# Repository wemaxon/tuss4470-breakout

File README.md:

# tuss4470-breakout
Breakout Board for the TUSS4470 Ultrasonic Sensing IC

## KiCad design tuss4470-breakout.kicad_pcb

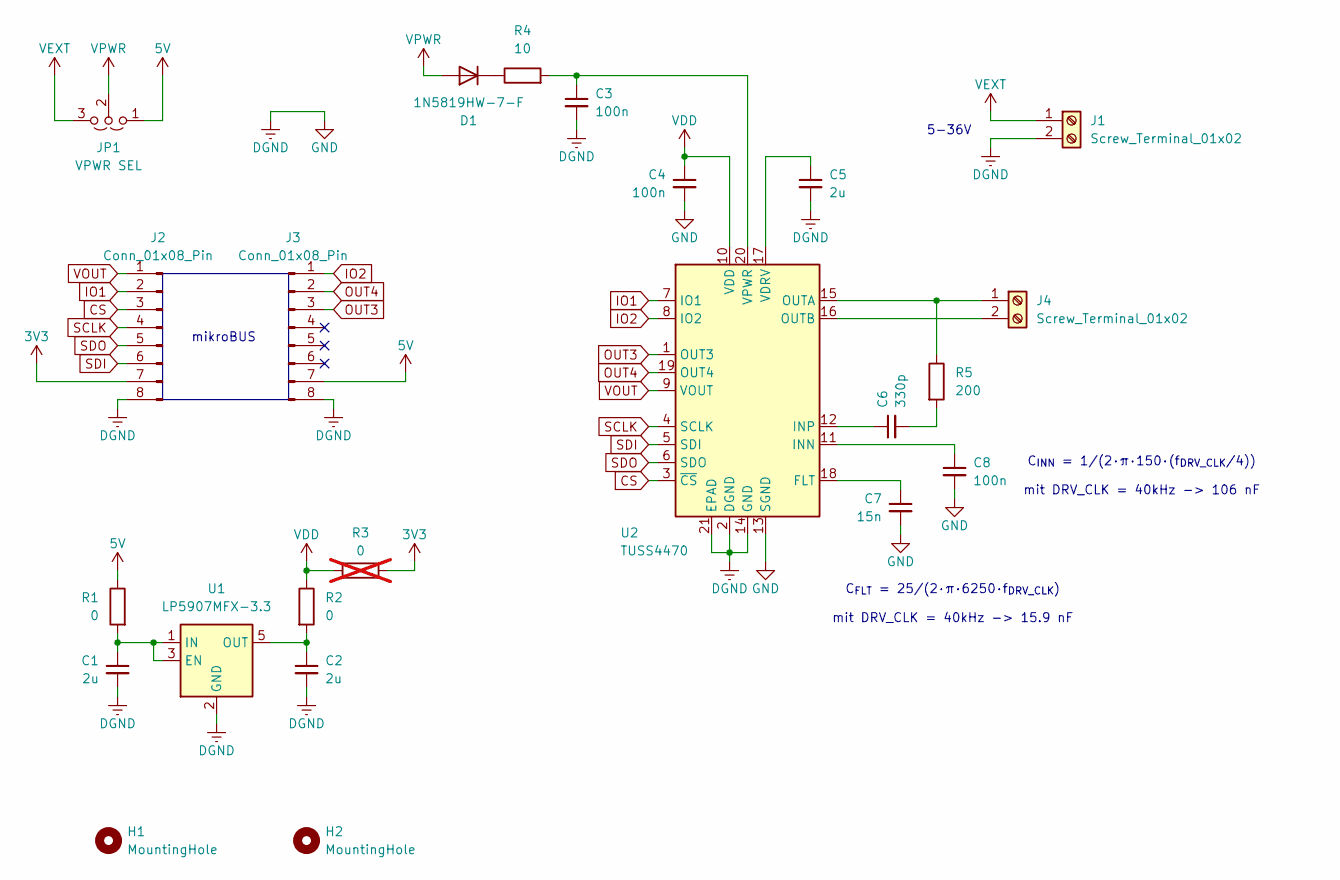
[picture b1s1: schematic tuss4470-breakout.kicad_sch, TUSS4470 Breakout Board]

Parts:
C1, C2, C5: 2u; C_0603_1608Metric; LCSC Part C913904
C3, C4, C8: 100n; C_0603_1608Metric; LCSC Part C14663
C6: 330p; C_0603_1608Metric; LCSC Part C1664
C7: 15n; C_0603_1608Metric; LCSC Part C519550
D1: 1N5819HW-7-F; D_SOD-123; LCSC Part C82544
H1, H2: MountingHole; MountingHole_3.2mm_M3
J1, J4: Screw_Terminal_01x02; TerminalBlock_Xinya_XY308-2.54-2P_1x02_P2.54mm_Horizontal; LCSC Part C557685
J2, J3: Conn_01x08_Pin; PinHeader_1x08_P2.54mm_Vertical
JP1: VPWR SEL; PinHeader_1x03_P2.54mm_Vertical
R1, R2: 0; R_0603_1608Metric; LCSC Part C95177
R3: 0; R_0603_1608Metric; LCSC Part C95177; not fitted
R4: 10; R_0805_2012Metric; LCSC Part C441940
R5: 200; R_0805_2012Metric; LCSC Part C5972814
U1: LP5907MFX-3.3; SOT-23-5; LCSC Part C80670
U2: TUSS4470; WQFN-20-1EP_4x4mm_P0.5mm_EP2.7x2.7mm_ThermalVias; LCSC Part C1855776

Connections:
3V3: J2.7, R3.1
5V: J3.7, JP1.1 (A), R1.1
CS: J2.3, U2.3 (~CS)
DGND: C1.2, C2.2, C3.2, C4.2, C5.2, C7.2, C8.2, J1.2, J2.8, J3.8, U1.2 (GND), U2.2 (DGND), U2.13 (SGND), U2.14 (GND), U2.21 (EPAD)
IO1: J2.2, U2.7 (IO1)
IO2: J3.1, U2.8 (IO2)
unnamed: C6.2, R5.2
unnamed: D1.1 (K), R4.1
unnamed: J4.1, R5.1, U2.15 (OUTA)
unnamed: J4.2, U2.16 (OUTB)
unnamed: C1.1, R1.2, U1.1 (IN), U1.3 (EN)
unnamed: C2.1, R2.2, U1.5 (OUT)
unnamed: C7.1, U2.18 (FLT)
unnamed: C8.1, U2.11 (INN)
unnamed: C6.1, U2.12 (INP)
unnamed: C5.1, U2.17 (VDRV)
unnamed: C3.1, R4.2, U2.20 (VPWR)
OUT3: J3.3, U2.1 (OUT3)
OUT4: J3.2, U2.19 (OUT4)
SCLK: J2.4, U2.4 (SCLK)
SDI: J2.6, U2.5 (SDI)
SDO: J2.5, U2.6 (SDO)
VDD: C4.1, R2.1, R3.2, U2.10 (VDD)
VEXT: J1.1, JP1.3 (B)
VOUT: J2.1, U2.9 (VOUT)
VPWR: D1.2 (A), JP1.2 (C)

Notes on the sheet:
5-36V
mikroBUS
C_{FLT} = 25/(2·π·6250·f_{DRV_CLK}) mit DRV_CLK = 40kHz -> 15.9 nF
C_{INN} = 1/(2·π·150·(f_{DRV_CLK}/4)) mit DRV_CLK = 40kHz -> 106 nF

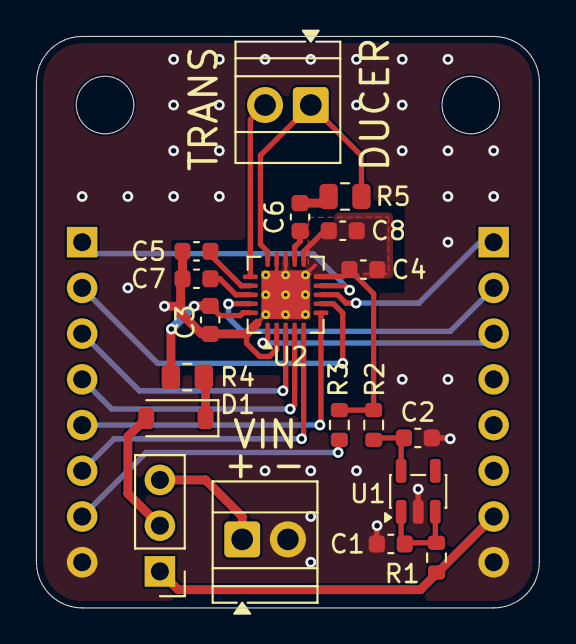
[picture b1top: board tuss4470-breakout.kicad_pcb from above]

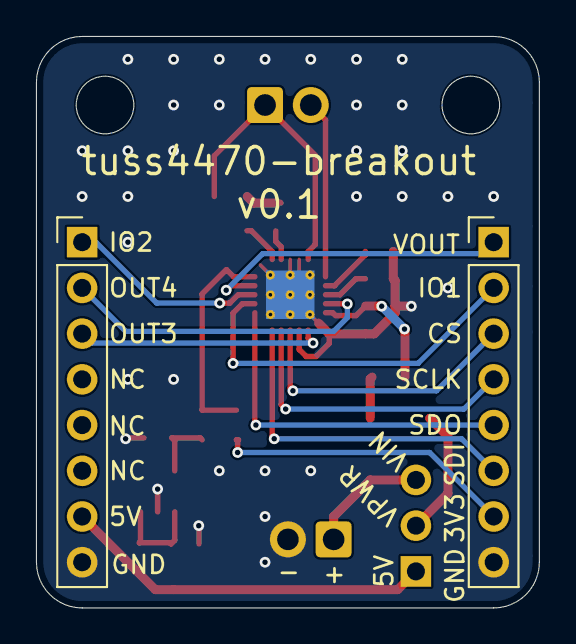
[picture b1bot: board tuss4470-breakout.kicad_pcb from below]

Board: 4 copper layers, 27.9 x 31.8 mm, 23 parts (2 on the bottom side), 26 nets.

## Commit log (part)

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2026-05-18 add gitignore, continue schematic
2026-05-18 layout finished
2026-05-18 generate gerbers
2026-05-19 v0.1 ordered pcb and components
